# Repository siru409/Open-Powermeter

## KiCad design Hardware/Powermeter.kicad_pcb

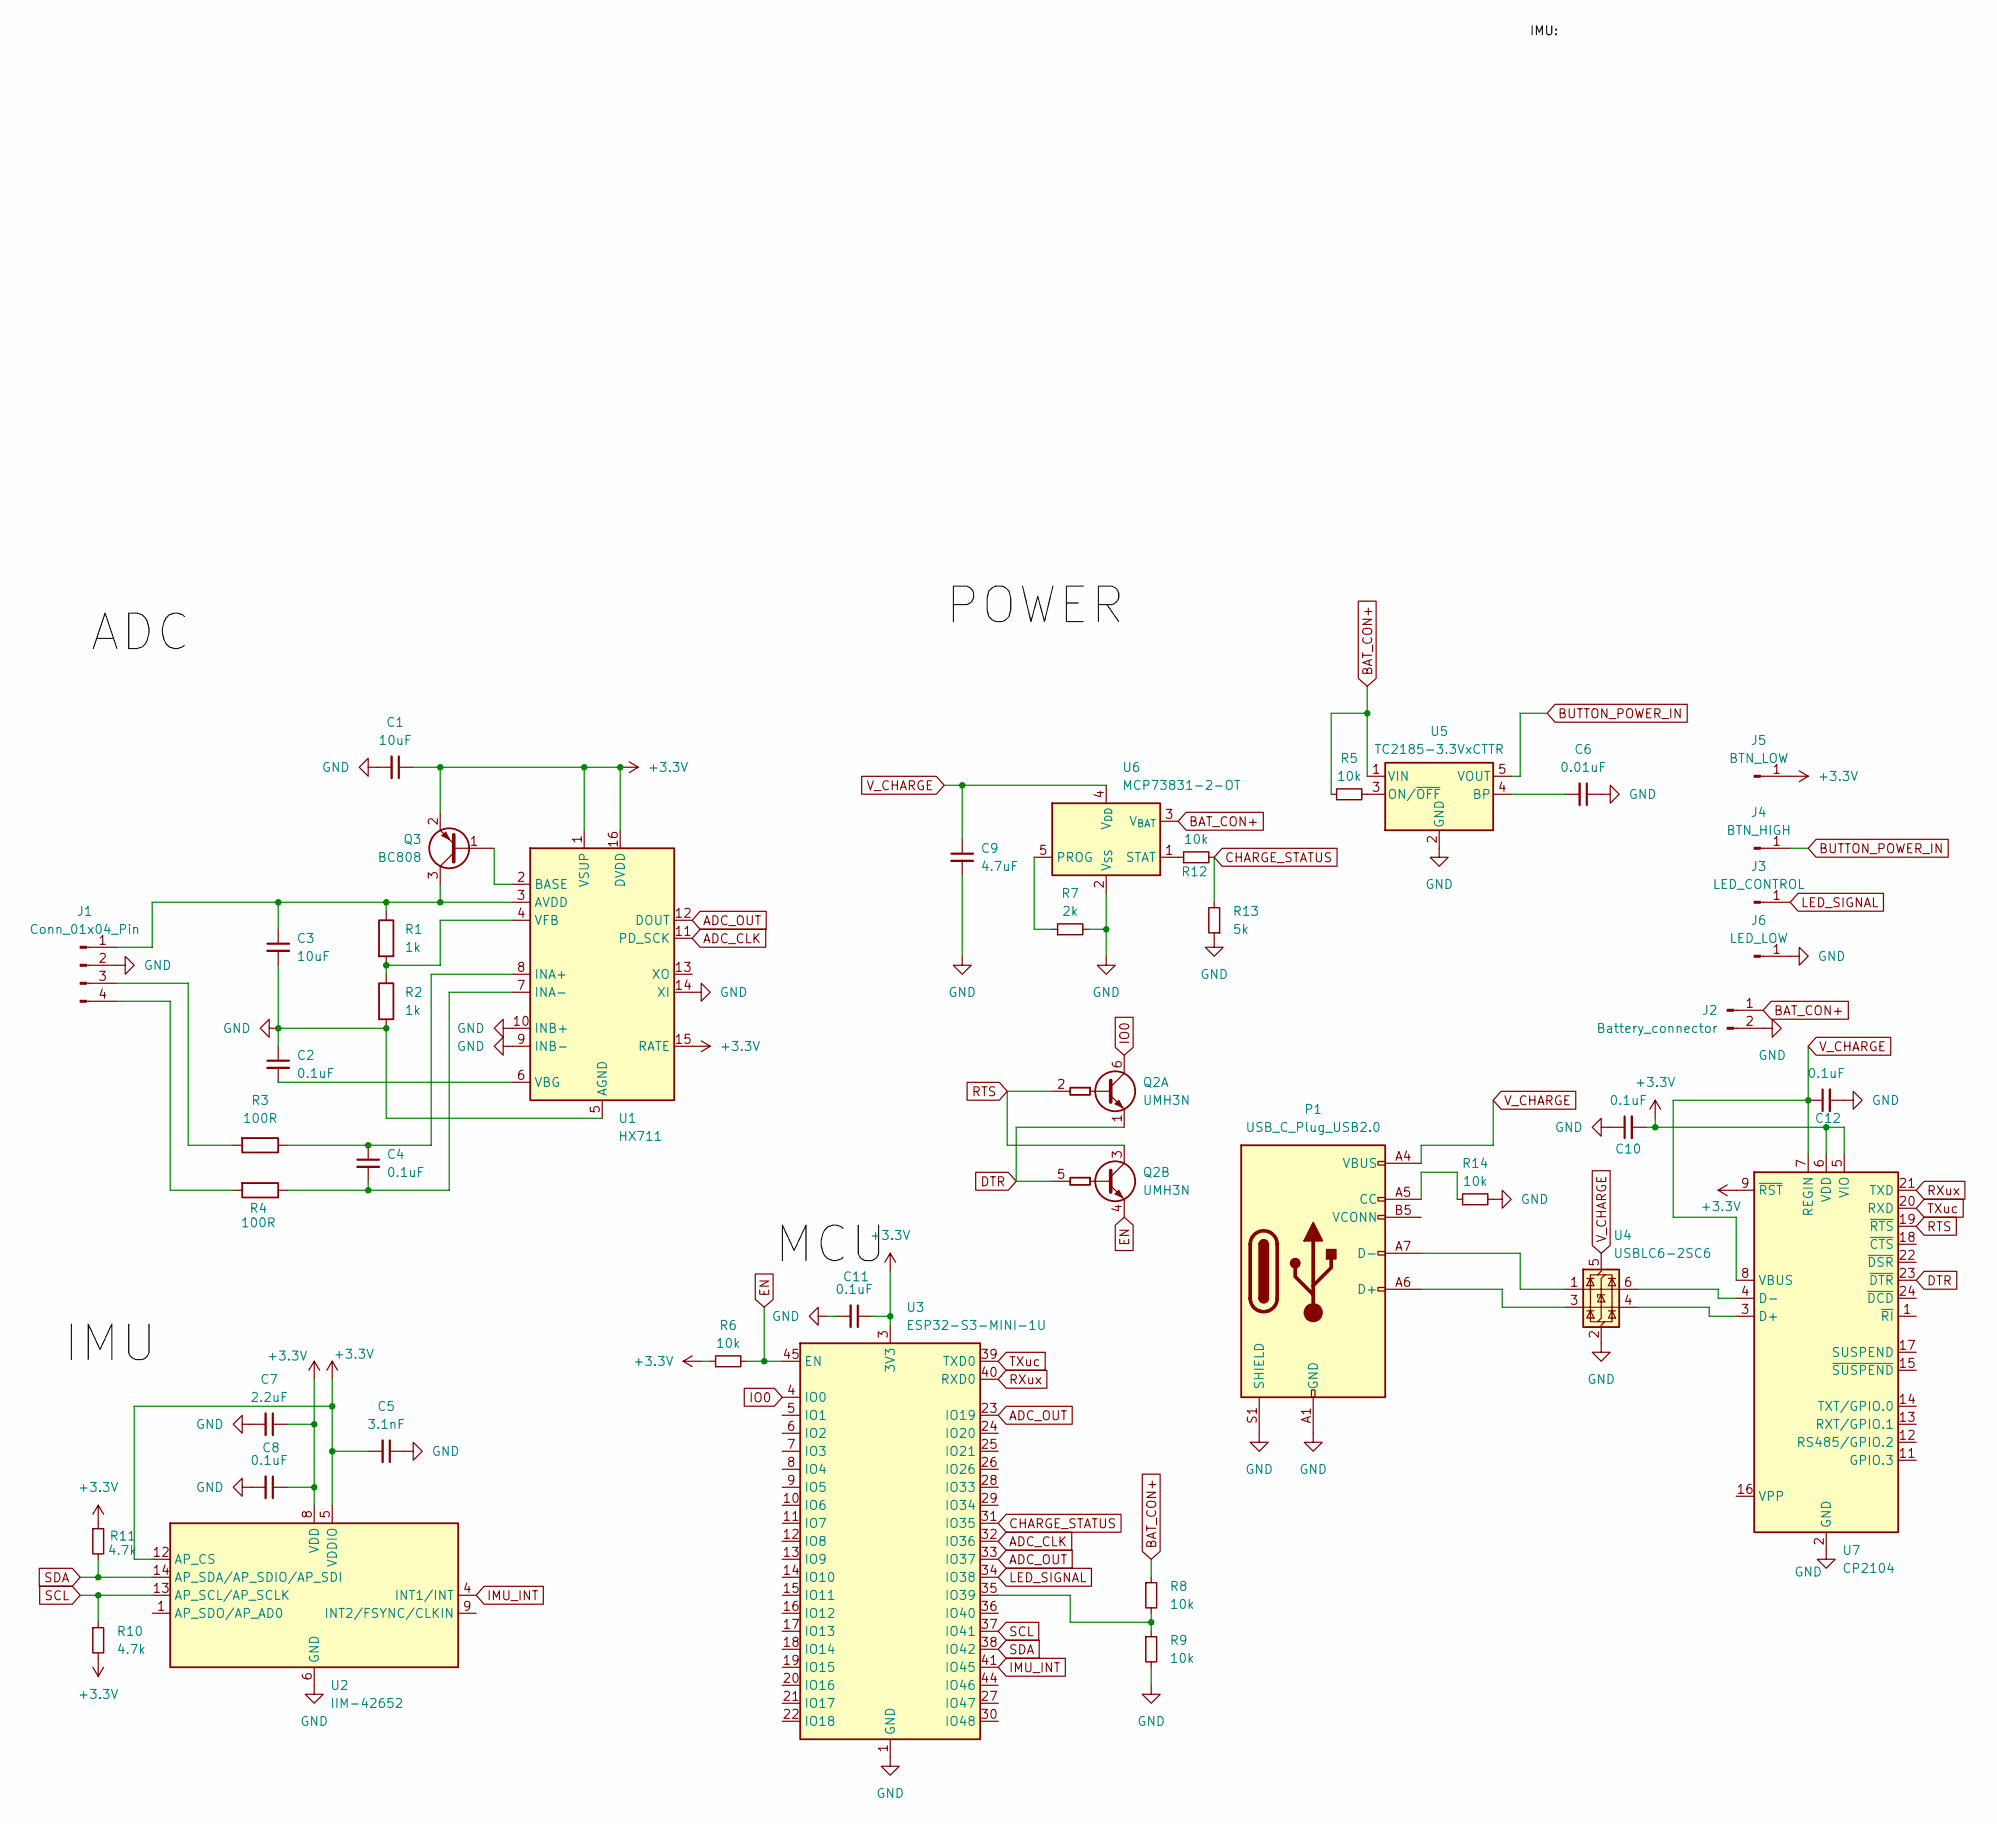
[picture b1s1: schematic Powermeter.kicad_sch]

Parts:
C1, C3: 10uF; C_0402_1005Metric
C2, C4, C8, C10, C11, C12: 0.1uF; C_0402_1005Metric
C5: 3.1nF; C_0402_1005Metric
C6: 0.01uF; C_0402_1005Metric
C7: 2.2uF; C_0402_1005Metric
C9: 4.7uF; C_0402_1005Metric
J1: Conn_01x04_Pin; JST_ACH_BM04B-ACHSS-A-GAN-ETF_1x04-1MP_P1.20mm_Vertical
J2: Battery_connector; JST_ACH_BM02B-ACHSS-GAN-ETF_1x02-1MP_P1.20mm_Vertical
J3: LED_CONTROL; TestPoint_Pad_3.0x3.0mm
J4: BTN_HIGH; TestPoint_Pad_3.0x3.0mm
J5: BTN_LOW; TestPoint_Pad_3.0x3.0mm
J6: LED_LOW; TestPoint_Pad_3.0x3.0mm
P1: USB_C_Plug_USB2.0; USB_C_Receptacle_GCT_USB4105-xx-A_16P_TopMnt_Horizontal
Q2: UMH3N; SOT-363_SC-70-6
Q3: BC808; SOT-23
R1, R2: 1k; R_0402_1005Metric
R3, R4: 100R; R_0402_1005Metric
R5, R6, R12, R14: 10k; R_0402_1005Metric
R7: 2k; R_0402_1005Metric
R8, R9: 10k; C_0402_1005Metric
R10, R11: 4.7k; R_0402_1005Metric
R13: 5k; R_0402_1005Metric
U1: HX711; SOP-16_3.9x9.9mm_P1.27mm
U2: IIM-42652; Bosch_LGA-14_3x2.5mm_P0.5mm
U3: ESP32-S3-MINI-1U; ESP32-S2-MINI-1U
U4: USBLC6-2SC6; SOT-23-6
U5: TC2185-3.3VxCTTR; SOT-23-5
U6: MCP73831-2-OT; SOT-23-5
U7: CP2104; QFN-24-1EP_4x4mm_P0.5mm_EP2.6x2.6mm

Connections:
+3.3V: C1.1, C5.2, C7.1, C8.1, C10.2, C11.1, J5.1, Q3.2 (E), R6.1, R10.2, R11.1, U1.1 (VSUP), U1.15 (RATE), U1.16 (DVDD), U2.5 (VDDIO), U2.8 (VDD), U2.12 (AP_CS), U3.3 (3V3), U7.5 (VIO), U7.6 (VDD), U7.9 (~RST)
ADC_CLK: U1.11 (PD_SCK), U3.32 (IO36)
ADC_OUT: U1.12 (DOUT), U3.23 (IO19), U3.33 (IO37)
BAT_CON+: J2.1, R5.1, R8.1, U5.1 (VIN), U6.3 (V_{BAT})
BUTTON_POWER_IN: J4.1, U5.5 (VOUT)
CHARGE_STATUS: R12.2, R13.2, U3.31 (IO35)
DTR: Q2.1 (E1), Q2.5 (B2), U7.23 (~DTR)
EN: Q2.4 (E2), R6.2, U3.45 (EN)
GND: C1.2, C2.1, C3.2, C5.1, C6.1, C7.2, C8.2, C9.2, C10.1, C11.2, C12.2, J1.2, J2.2, J6.1, P1.A1 (GND), P1.A12 (GND), P1.B1 (GND), P1.B12 (GND), P1.S1 (SHIELD), R2.2, R7.2, R9.2, R13.1, R14.2, U1.5 (AGND), U1.9 (INB-), U1.10 (INB+), U1.14 (XI), U2.6 (GND), U2.7 (GND), U3.1 (GND), U3.2 (GND), U3.42 (GND), U3.43 (GND), U3.46 (GND), U3.47 (GND), U3.48 (GND), U3.49 (GND), U3.50 (GND), U3.51 (GND), U3.52 (GND), U3.53 (GND), U3.54 (GND), U3.55 (GND), U3.56 (GND), U3.57 (GND), U3.58 (GND), U3.59 (GND), U3.60 (GND), U3.61 (GND), U3.62 (GND), U3.63 (GND), U3.64 (GND), U3.65 (GND), U4.2 (GND), U5.2 (GND), U6.2 (V_{SS}), U7.2 (GND), U7.25 (GND)
IMU_INT: U2.4 (INT1/INT), U3.41 (IO45)
IO0: Q2.6 (C1), U3.4 (IO0)
LED_SIGNAL: J3.1, U3.34 (IO38)
unnamed: C3.1, J1.1, Q3.3 (C), R1.1, U1.3 (AVDD)
unnamed: J1.3, R3.2
unnamed: J1.4, R4.2
unnamed: P1.A5 (CC), R14.1
unnamed: P1.A6 (D+), U4.3 (I/O2)
unnamed: P1.A7 (D-), U4.1 (I/O1)
unnamed: Q3.1 (B), U1.2 (BASE)
unnamed: C4.1, R3.1, U1.8 (INA+)
unnamed: C4.2, R4.1, U1.7 (INA-)
unnamed: C2.2, U1.6 (VBG)
unnamed: R1.2, R2.1, U1.4 (VFB)
unnamed: R8.2, R9.1, U3.35 (IO39)
unnamed: C6.2, U5.4 (BP)
unnamed: R5.2, U5.3 (ON/~OFF)
unnamed: R7.1, U6.5 (PROG)
unnamed: R12.1, U6.1 (STAT)
unnamed: U4.4 (I/O2), U7.3 (D+)
unnamed: U4.6 (I/O1), U7.4 (D-)
RTS: Q2.2 (B1), Q2.3 (C2), U7.19 (~RTS)
RXux: U3.40 (RXD0), U7.21 (TXD)
SCL: R10.1, U2.13 (AP_SCL/AP_SCLK), U3.37 (IO41)
SDA: R11.2, U2.14 (AP_SDA/AP_SDIO/AP_SDI), U3.38 (IO42)
TXuc: U3.39 (TXD0), U7.20 (RXD)
V_CHARGE: C9.1, C12.1, P1.A4 (VBUS), P1.A9 (VBUS), P1.B4 (VBUS), P1.B9 (VBUS), U4.5 (VBUS), U6.4 (V_{DD}), U7.7 (REGIN), U7.8 (VBUS)

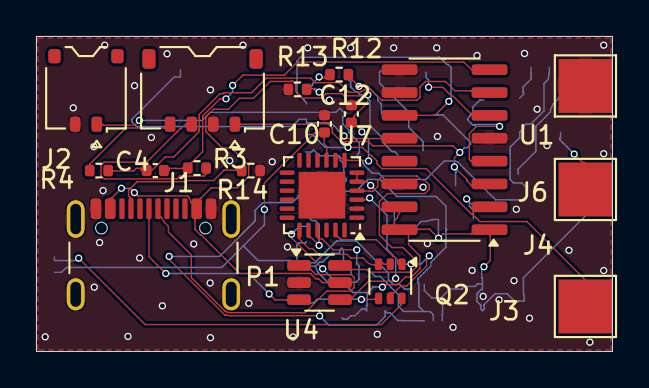
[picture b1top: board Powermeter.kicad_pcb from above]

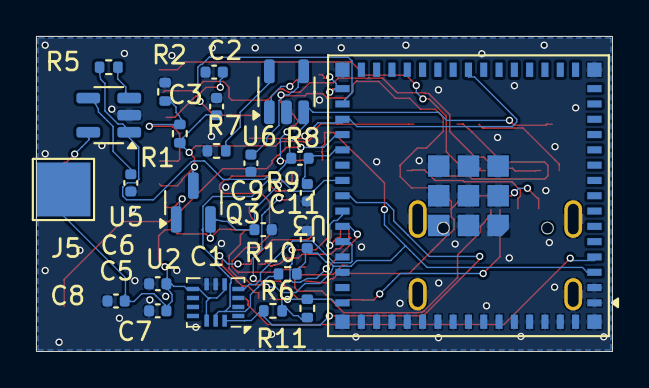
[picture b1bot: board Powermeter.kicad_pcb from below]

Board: 2 copper layers, 32.0 x 17.5 mm, 42 parts (24 on the bottom side), 36 nets.

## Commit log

2024-09-28 Added Hardware design
